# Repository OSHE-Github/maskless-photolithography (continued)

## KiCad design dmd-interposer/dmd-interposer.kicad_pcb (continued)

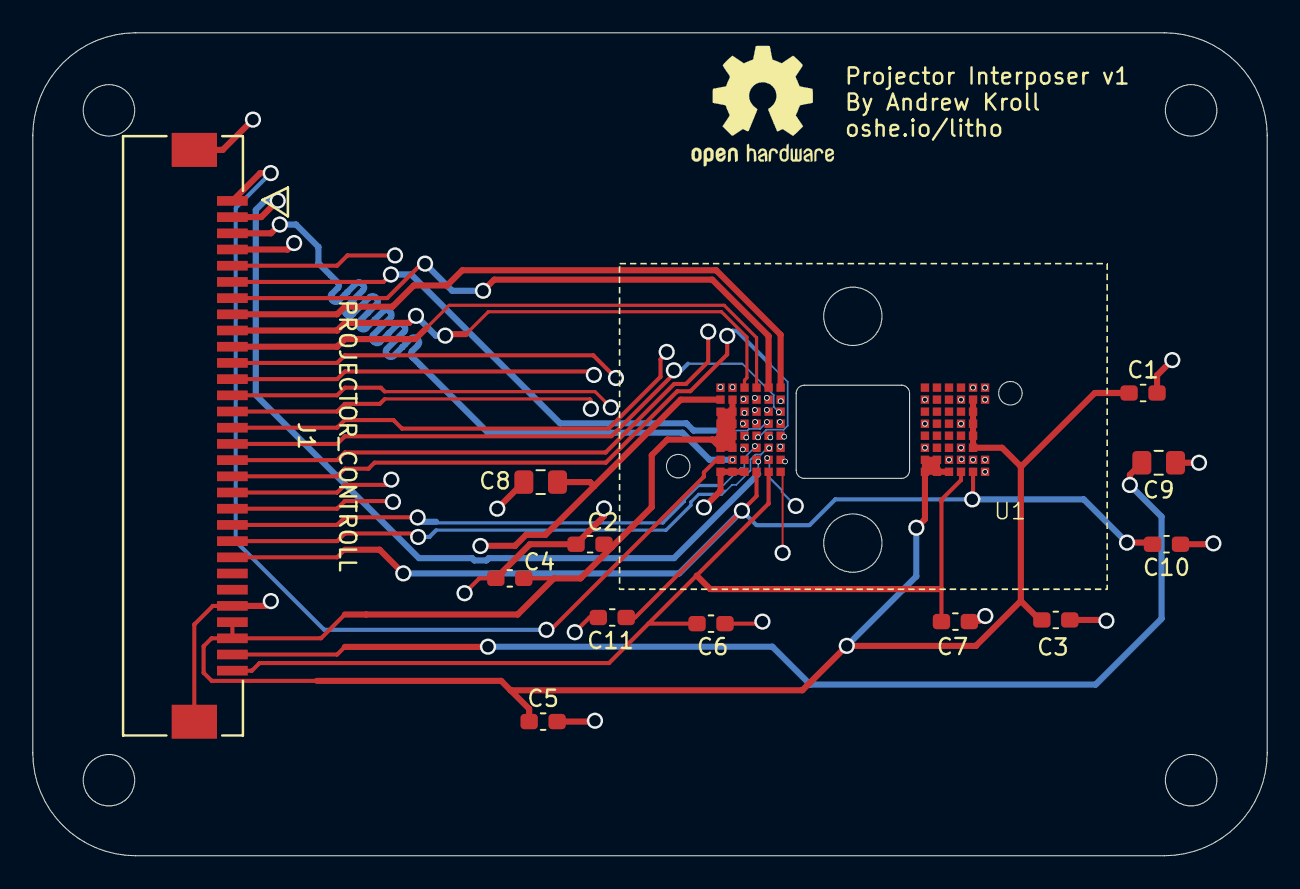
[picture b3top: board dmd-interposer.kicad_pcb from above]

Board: 4 copper layers, 76.2 x 50.8 mm, 13 parts (0 on the bottom side), 27 nets.

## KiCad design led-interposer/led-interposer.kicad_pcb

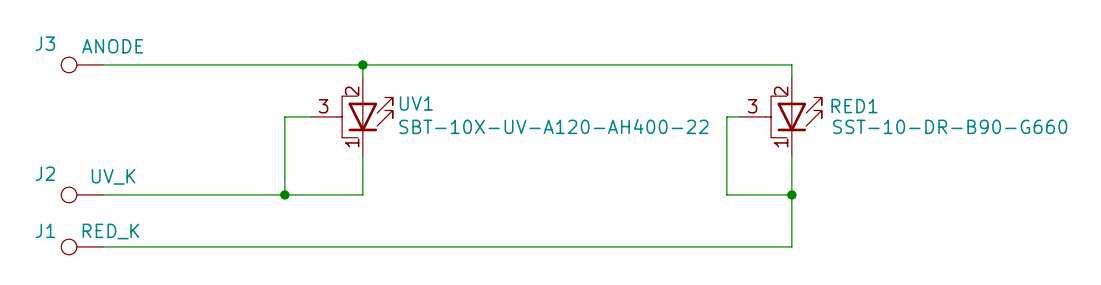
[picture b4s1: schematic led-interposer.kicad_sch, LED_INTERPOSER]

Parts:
J1: RED_K; TespointBig
J2: UV_K; TespointBig
J3: ANODE; TespointBig
RED1: SST-10-DR-B90-G660; LED_SST-10-DR-B90-G660; Digikey 1214-1436-1-ND
UV1: SBT-10X-UV-A120-AH400-22; LED_SBT-10X-UV-A120-AH400-22; Digikey 1214-SBT-10X-UV-A120-AH400-22CT-ND

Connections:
unnamed: J3.1 (1_1), RED1.2 (A), UV1.2 (A)
unnamed: J1.1 (1_1), RED1.1 (K), RED1.3 (PAD)
unnamed: J2.1 (1_1), UV1.1 (K), UV1.3 (PAD)

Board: 2 copper layers, 5 parts (0 on the bottom side), 3 nets, no tracks yet.
